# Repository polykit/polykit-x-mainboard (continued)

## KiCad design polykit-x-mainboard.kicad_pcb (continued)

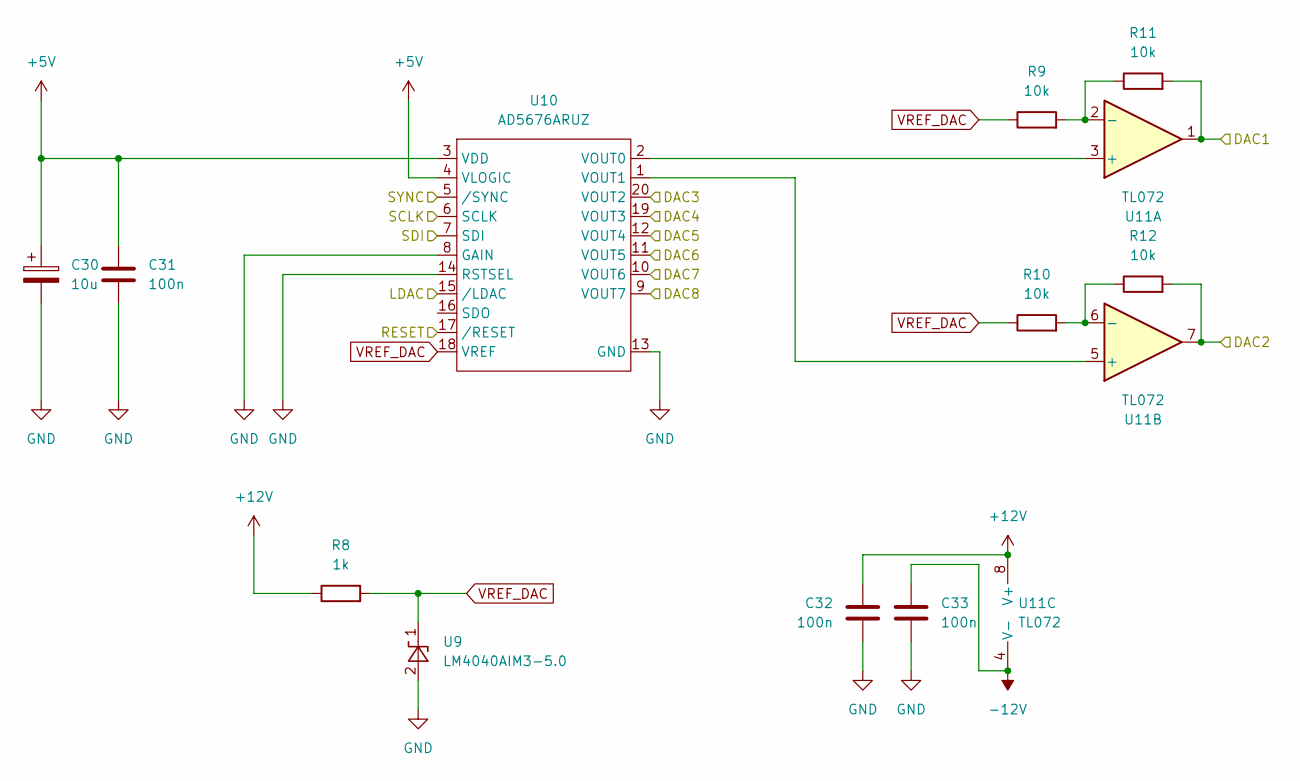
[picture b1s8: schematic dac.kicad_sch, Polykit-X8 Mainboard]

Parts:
C30: 10u; CP_Elec_5x5.9
C31, C32, C33: 100n; C_1206_3216Metric_Pad1.33x1.80mm_HandSolder
R8: 1k; R_1206_3216Metric_Pad1.30x1.75mm_HandSolder
R9, R10, R11, R12: 10k; R_1206_3216Metric_Pad1.30x1.75mm_HandSolder
U9: LM4040AIM3-5.0; SOT-23
U10: AD5676ARUZ; TSSOP-20_4.4x6.5mm_P0.65mm
U11: TL072; SO-8_3.9x4.9mm_P1.27mm

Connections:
+5V: C30.1, C31.1, U10.3 (VDD), U10.4 (VLOGIC); also elsewhere on the board
+12V: C32.1, R8.1, U11.8 (V+); also elsewhere on the board
-12V: C33.1, U11.4 (V-); also elsewhere on the board
/DAC/DAC1: R11.2, U11.1; also elsewhere on the board
/DAC/DAC3: U10.20 (VOUT2); also elsewhere on the board
/DAC/DAC4: U10.19 (VOUT3); also elsewhere on the board
/DAC/DAC7: U10.10 (VOUT6); also elsewhere on the board
/DAC/LDAC: U10.15 (/LDAC); also elsewhere on the board
/DAC/RESET: U10.17 (/RESET); also elsewhere on the board
DAC_FREQ: U10.11 (VOUT5); also elsewhere on the board
DAC_PAN: R12.2, U11.7; also elsewhere on the board
DAC_RES: U10.12 (VOUT4); also elsewhere on the board
DAC_SSYNC: U10.9 (VOUT7); also elsewhere on the board
GND: C30.2, C31.2, C32.2, C33.2, U9.2 (A), U10.8 (GAIN), U10.13 (GND), U10.14 (RSTSEL); also elsewhere on the board
MOSI: U10.7 (SDI); also elsewhere on the board
unnamed: R10.2, R12.1, U11.6 (-)
unnamed: R9.2, R11.1, U11.2 (-)
unnamed: U10.1 (VOUT1), U11.5 (+)
unnamed: U10.2 (VOUT0), U11.3 (+)
SCK: U10.6 (SCLK); also elsewhere on the board
SS: U10.5 (/SYNC); also elsewhere on the board
VREF_DAC: R8.2, R9.1, R10.1, U9.1 (K), U10.18 (VREF)

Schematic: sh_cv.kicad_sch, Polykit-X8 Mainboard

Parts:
C15, C16, C17, C18, C23, C24, C25: 100n; C_1206_3216Metric_Pad1.33x1.80mm_HandSolder
C19, C20, C21, C22, C26, C27, C28, C29: 10n; C_1206_3216Metric_Pad1.33x1.80mm_HandSolder
R2, R3, R4, R5, R6, R7: 100k; R_1206_3216Metric_Pad1.30x1.75mm_HandSolder
U5: CD4051B; SO-16_5.3x10.2mm_P1.27mm
U6, U7, U8: TL074; SO-14_3.9x8.65mm_P1.27mm

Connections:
+5V: C15.1, U5.16 (VDD); also elsewhere on the board
+12V: C16.1, C18.1, C24.1, U6.4 (V+), U7.4 (V+), U8.4 (V+); also elsewhere on the board
-12V: C17.1, C23.1, C25.1, U6.11 (V-), U7.11 (V-), U8.11 (V-); also elsewhere on the board
/DAC/DAC7: U5.3 (X); also elsewhere on the board
DAC_ADSR_A: R5.2, U8.14; also elsewhere on the board
DAC_ADSR_D: R6.2, U8.8; also elsewhere on the board
DAC_ADSR_R: R7.2, U7.7; also elsewhere on the board
DAC_ADSR_S: U6.8, U6.9 (-); also elsewhere on the board
DAC_HSYNC: U8.6 (-), U8.7; also elsewhere on the board
DAC_LEVEL1: U7.8, U7.9 (-); also elsewhere on the board
DAC_LEVEL2: U7.13 (-), U7.14; also elsewhere on the board
DAC_PWM: U8.1, U8.2 (-); also elsewhere on the board
GND: C15.2, C16.2, C17.2, C18.2, C19.2, C20.2, C21.2, C22.2, C23.2, C24.2, C25.2, C26.2, C27.2, C28.2, C29.2, U5.6 (INH), U5.7 (VEE), U5.8 (VSS), U7.3 (+), U7.5 (+), U8.10 (+), U8.12 (+); also elsewhere on the board
unnamed: C19.1, U5.14 (X1), U6.3 (+)
unnamed: C20.1, U5.13 (X0), U6.5 (+)
unnamed: C21.1, U5.12 (X3), U6.10 (+)
unnamed: C22.1, U5.15 (X2), U6.12 (+)
unnamed: C26.1, U5.5 (X5), U7.10 (+)
unnamed: C27.1, U5.1 (X4), U7.12 (+)
unnamed: C28.1, U5.2 (X6), U8.3 (+)
unnamed: C29.1, U5.4 (X7), U8.5 (+)
unnamed: R2.1, U6.1, U6.2 (-)
unnamed: R2.2, R5.1, U8.13 (-)
unnamed: R3.1, U6.6 (-), U6.7
unnamed: R3.2, R6.1, U8.9 (-)
unnamed: R4.1, U6.13 (-), U6.14
unnamed: R4.2, R7.1, U7.6 (-)
unnamed: U7.1, U7.2 (-)
SH_CV_A: U5.11 (A); also elsewhere on the board
SH_CV_B: U5.10 (B); also elsewhere on the board
SH_CV_C: U5.9 (C); also elsewhere on the board

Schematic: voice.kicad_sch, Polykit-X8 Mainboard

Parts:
R1: 100k; R_1206_3216Metric_Pad1.30x1.75mm_HandSolder
VOICE1: VOICE; PinSocket_1x36_P2.54mm_Vertical

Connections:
+5V: VOICE1.4; also elsewhere on the board
+12V: VOICE1.2; also elsewhere on the board
-5V: VOICE1.5; also elsewhere on the board
-12V: VOICE1.3; also elsewhere on the board
/VOICES/VOICE1/ADSR_OUT: VOICE1.17
DAC_ADSR_A: VOICE1.11; also elsewhere on the board
DAC_ADSR_D: VOICE1.12; also elsewhere on the board
DAC_ADSR_R: VOICE1.14; also elsewhere on the board
DAC_ADSR_S: VOICE1.13; also elsewhere on the board
DAC_FREQ: VOICE1.30; also elsewhere on the board
DAC_HSYNC: VOICE1.10; also elsewhere on the board
DAC_LEVEL1: VOICE1.25; also elsewhere on the board
DAC_LEVEL2: VOICE1.26; also elsewhere on the board
DAC_PAN: VOICE1.28; also elsewhere on the board
DAC_PWM: VOICE1.7; also elsewhere on the board
DAC_RES: VOICE1.31; also elsewhere on the board
DAC_SSYNC: VOICE1.9; also elsewhere on the board
EXTERNAL_IN: VOICE1.29; also elsewhere on the board
FM1: VOICE1.8; also elsewhere on the board
GATE1: VOICE1.16; also elsewhere on the board
GND: VOICE1.1; also elsewhere on the board
unnamed: R1.1, VOICE1.6
OUT_L1: VOICE1.35; also elsewhere on the board
OUT_R1: VOICE1.36; also elsewhere on the board
PITCH1: R1.2; also elsewhere on the board
SW_EXTERNAL_ON: VOICE1.20; also elsewhere on the board
SW_FILTER_MODE_A: VOICE1.32; also elsewhere on the board
SW_FILTER_MODE_B: VOICE1.33; also elsewhere on the board
SW_FILTER_MODE_C: VOICE1.34; also elsewhere on the board
SW_FREQ_ADSR: VOICE1.22; also elsewhere on the board
SW_FREQ_ADSR_NEG: VOICE1.21; also elsewhere on the board
SW_RES_ADSR: VOICE1.23; also elsewhere on the board
SW_RES_ADSR_NEG: VOICE1.24; also elsewhere on the board
SW_SAW_ON: VOICE1.18; also elsewhere on the board
SW_TRIANGLE_ON: VOICE1.19; also elsewhere on the board
TRIG1: VOICE1.15; also elsewhere on the board
VCA1: VOICE1.27; also elsewhere on the board

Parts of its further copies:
R13, R14, R15, R16, R17, R18, R19: 100k; R_1206_3216Metric_Pad1.30x1.75mm_HandSolder
VOICE2, VOICE3, VOICE4, VOICE5, VOICE6, VOICE7, VOICE8: VOICE; PinSocket_1x36_P2.54mm_Vertical

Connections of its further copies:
+5V: VOICE2.4, VOICE3.4, VOICE4.4, VOICE5.4, VOICE6.4, VOICE7.4, VOICE8.4; also elsewhere on the board
+12V: VOICE2.2, VOICE3.2, VOICE4.2, VOICE5.2, VOICE6.2, VOICE7.2, VOICE8.2; also elsewhere on the board
-5V: VOICE2.5, VOICE3.5, VOICE4.5, VOICE5.5, VOICE6.5, VOICE7.5, VOICE8.5; also elsewhere on the board
-12V: VOICE2.3, VOICE3.3, VOICE4.3, VOICE5.3, VOICE6.3, VOICE7.3, VOICE8.3; also elsewhere on the board
/VOICES/VOICE2/ADSR_OUT: VOICE2.17
/VOICES/VOICE3/ADSR_OUT: VOICE3.17
/VOICES/VOICE4/ADSR_OUT: VOICE4.17
/VOICES/VOICE5/ADSR_OUT: VOICE5.17
/VOICES/VOICE6/ADSR_OUT: VOICE6.17
/VOICES/VOICE7/ADSR_OUT: VOICE7.17
/VOICES/VOICE8/ADSR_OUT: VOICE8.17
DAC_ADSR_A: VOICE2.11, VOICE3.11, VOICE4.11, VOICE5.11, VOICE6.11, VOICE7.11, VOICE8.11; also elsewhere on the board
DAC_ADSR_D: VOICE2.12, VOICE3.12, VOICE4.12, VOICE5.12, VOICE6.12, VOICE7.12, VOICE8.12; also elsewhere on the board
DAC_ADSR_R: VOICE2.14, VOICE3.14, VOICE4.14, VOICE5.14, VOICE6.14, VOICE7.14, VOICE8.14; also elsewhere on the board
DAC_ADSR_S: VOICE2.13, VOICE3.13, VOICE4.13, VOICE5.13, VOICE6.13, VOICE7.13, VOICE8.13; also elsewhere on the board
DAC_FREQ: VOICE2.30, VOICE3.30, VOICE4.30, VOICE5.30, VOICE6.30, VOICE7.30, VOICE8.30; also elsewhere on the board
DAC_HSYNC: VOICE2.10, VOICE3.10, VOICE4.10, VOICE5.10, VOICE6.10, VOICE7.10, VOICE8.10; also elsewhere on the board
DAC_LEVEL1: VOICE2.25, VOICE3.25, VOICE4.25, VOICE5.25, VOICE6.25, VOICE7.25, VOICE8.25; also elsewhere on the board
DAC_LEVEL2: VOICE2.26, VOICE3.26, VOICE4.26, VOICE5.26, VOICE6.26, VOICE7.26, VOICE8.26; also elsewhere on the board
DAC_PAN: VOICE2.28, VOICE3.28, VOICE4.28, VOICE5.28, VOICE6.28, VOICE7.28, VOICE8.28; also elsewhere on the board
DAC_PWM: VOICE2.7, VOICE3.7, VOICE4.7, VOICE5.7, VOICE6.7, VOICE7.7, VOICE8.7; also elsewhere on the board
DAC_RES: VOICE2.31, VOICE3.31, VOICE4.31, VOICE5.31, VOICE6.31, VOICE7.31, VOICE8.31; also elsewhere on the board
DAC_SSYNC: VOICE2.9, VOICE3.9, VOICE4.9, VOICE5.9, VOICE6.9, VOICE7.9, VOICE8.9; also elsewhere on the board
EXTERNAL_IN: VOICE2.29, VOICE3.29, VOICE4.29, VOICE5.29, VOICE6.29, VOICE7.29, VOICE8.29; also elsewhere on the board
FM2: VOICE2.8; also elsewhere on the board
FM3: VOICE3.8; also elsewhere on the board
FM4: VOICE4.8; also elsewhere on the board
FM5: VOICE5.8; also elsewhere on the board
FM6: VOICE6.8; also elsewhere on the board
FM7: VOICE7.8; also elsewhere on the board
FM8: VOICE8.8; also elsewhere on the board
GATE2: VOICE2.16; also elsewhere on the board
GATE3: VOICE3.16; also elsewhere on the board
GATE4: VOICE4.16; also elsewhere on the board
GATE5: VOICE5.16; also elsewhere on the board
GATE6: VOICE6.16; also elsewhere on the board
GATE7: VOICE7.16; also elsewhere on the board
GATE8: VOICE8.16; also elsewhere on the board
GND: VOICE2.1, VOICE3.1, VOICE4.1, VOICE5.1, VOICE6.1, VOICE7.1, VOICE8.1; also elsewhere on the board
unnamed: R13.1, VOICE2.6
unnamed: R14.1, VOICE3.6
unnamed: R15.1, VOICE4.6
unnamed: R16.1, VOICE5.6
unnamed: R17.1, VOICE6.6
unnamed: R18.1, VOICE7.6
unnamed: R19.1, VOICE8.6
OUT_L2: VOICE2.35; also elsewhere on the board
OUT_L3: VOICE3.35; also elsewhere on the board
OUT_L4: VOICE4.35; also elsewhere on the board
OUT_L5: VOICE5.35; also elsewhere on the board
OUT_L6: VOICE6.35; also elsewhere on the board
OUT_L7: VOICE7.35; also elsewhere on the board
OUT_L8: VOICE8.35; also elsewhere on the board
OUT_R2: VOICE2.36; also elsewhere on the board
OUT_R3: VOICE3.36; also elsewhere on the board
OUT_R4: VOICE4.36; also elsewhere on the board
OUT_R5: VOICE5.36; also elsewhere on the board
OUT_R6: VOICE6.36; also elsewhere on the board
OUT_R7: VOICE7.36; also elsewhere on the board
OUT_R8: VOICE8.36; also elsewhere on the board
PITCH2: R13.2; also elsewhere on the board
PITCH3: R14.2; also elsewhere on the board
PITCH4: R15.2; also elsewhere on the board
PITCH5: R16.2; also elsewhere on the board
PITCH6: R17.2; also elsewhere on the board
PITCH7: R18.2; also elsewhere on the board
PITCH8: R19.2; also elsewhere on the board
SW_EXTERNAL_ON: VOICE2.20, VOICE3.20, VOICE4.20, VOICE5.20, VOICE6.20, VOICE7.20, VOICE8.20; also elsewhere on the board
SW_FILTER_MODE_A: VOICE2.32, VOICE3.32, VOICE4.32, VOICE5.32, VOICE6.32, VOICE7.32, VOICE8.32; also elsewhere on the board
SW_FILTER_MODE_B: VOICE2.33, VOICE3.33, VOICE4.33, VOICE5.33, VOICE6.33, VOICE7.33, VOICE8.33; also elsewhere on the board
SW_FILTER_MODE_C: VOICE2.34, VOICE3.34, VOICE4.34, VOICE5.34, VOICE6.34, VOICE7.34, VOICE8.34; also elsewhere on the board
SW_FREQ_ADSR: VOICE2.22, VOICE3.22, VOICE4.22, VOICE5.22, VOICE6.22, VOICE7.22, VOICE8.22; also elsewhere on the board
SW_FREQ_ADSR_NEG: VOICE2.21, VOICE3.21, VOICE4.21, VOICE5.21, VOICE6.21, VOICE7.21, VOICE8.21; also elsewhere on the board
SW_RES_ADSR: VOICE2.23, VOICE3.23, VOICE4.23, VOICE5.23, VOICE6.23, VOICE7.23, VOICE8.23; also elsewhere on the board
SW_RES_ADSR_NEG: VOICE2.24, VOICE3.24, VOICE4.24, VOICE5.24, VOICE6.24, VOICE7.24, VOICE8.24; also elsewhere on the board
SW_SAW_ON: VOICE2.18, VOICE3.18, VOICE4.18, VOICE5.18, VOICE6.18, VOICE7.18, VOICE8.18; also elsewhere on the board
SW_TRIANGLE_ON: VOICE2.19, VOICE3.19, VOICE4.19, VOICE5.19, VOICE6.19, VOICE7.19, VOICE8.19; also elsewhere on the board
TRIG2: VOICE2.15; also elsewhere on the board
TRIG3: VOICE3.15; also elsewhere on the board
TRIG4: VOICE4.15; also elsewhere on the board
TRIG5: VOICE5.15; also elsewhere on the board
TRIG6: VOICE6.15; also elsewhere on the board
TRIG7: VOICE7.15; also elsewhere on the board
TRIG8: VOICE8.15; also elsewhere on the board
VCA2: VOICE2.27; also elsewhere on the board
VCA3: VOICE3.27; also elsewhere on the board
VCA4: VOICE4.27; also elsewhere on the board
VCA5: VOICE5.27; also elsewhere on the board
VCA6: VOICE6.27; also elsewhere on the board
VCA7: VOICE7.27; also elsewhere on the board
VCA8: VOICE8.27; also elsewhere on the board

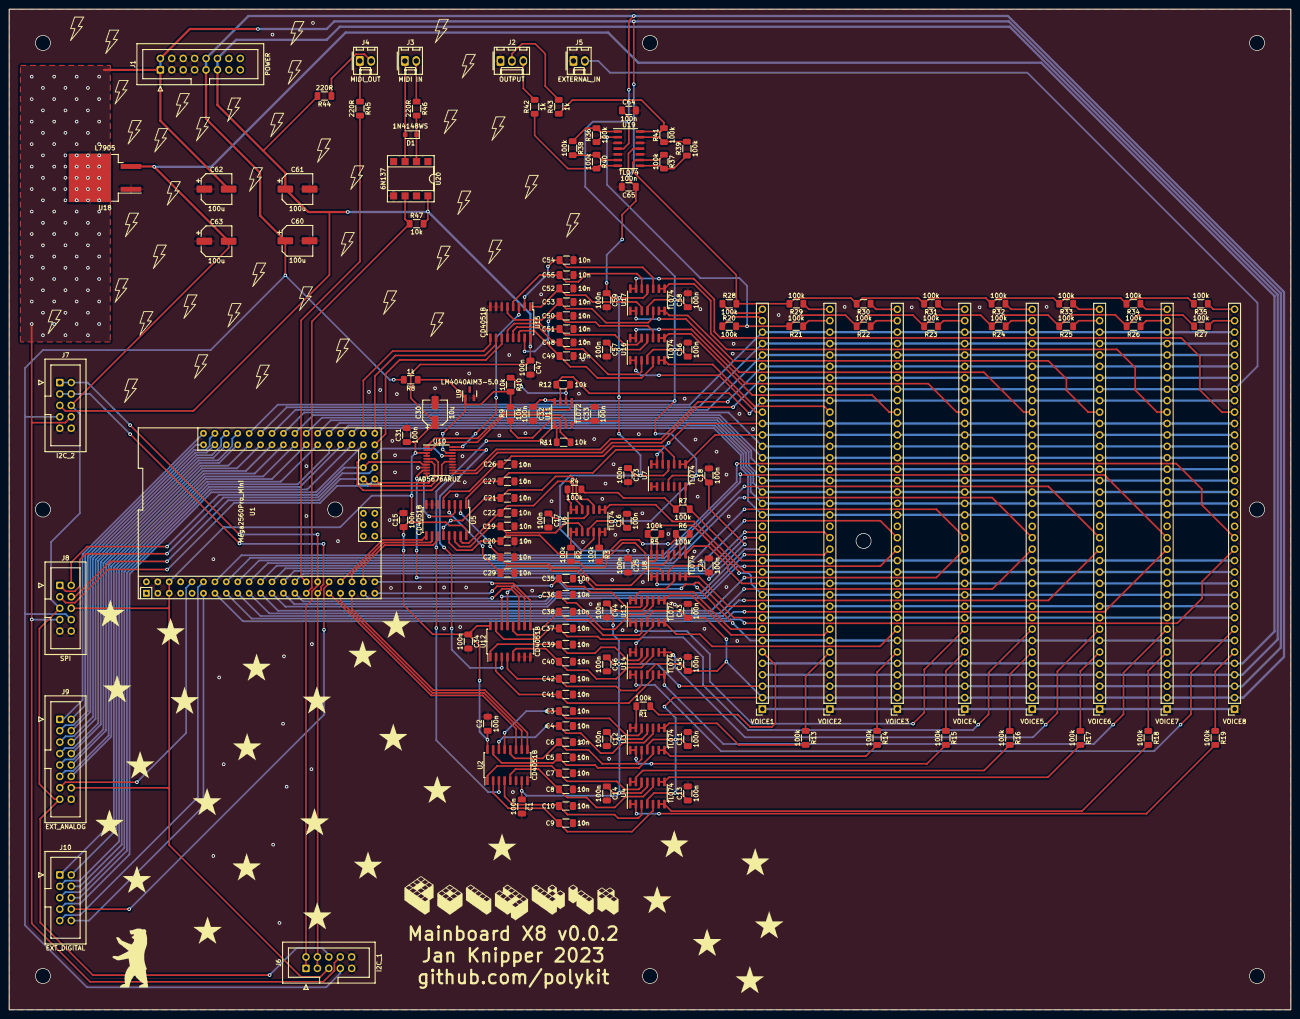
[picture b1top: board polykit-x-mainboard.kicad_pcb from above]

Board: 2 copper layers, 285.0 x 222.5 mm, 151 parts (0 on the bottom side), 200 nets.

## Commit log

2024-01-14 Initial import
2024-01-14 Add board rendering
2024-01-14 Add BOM
2025-05-09 Add license
